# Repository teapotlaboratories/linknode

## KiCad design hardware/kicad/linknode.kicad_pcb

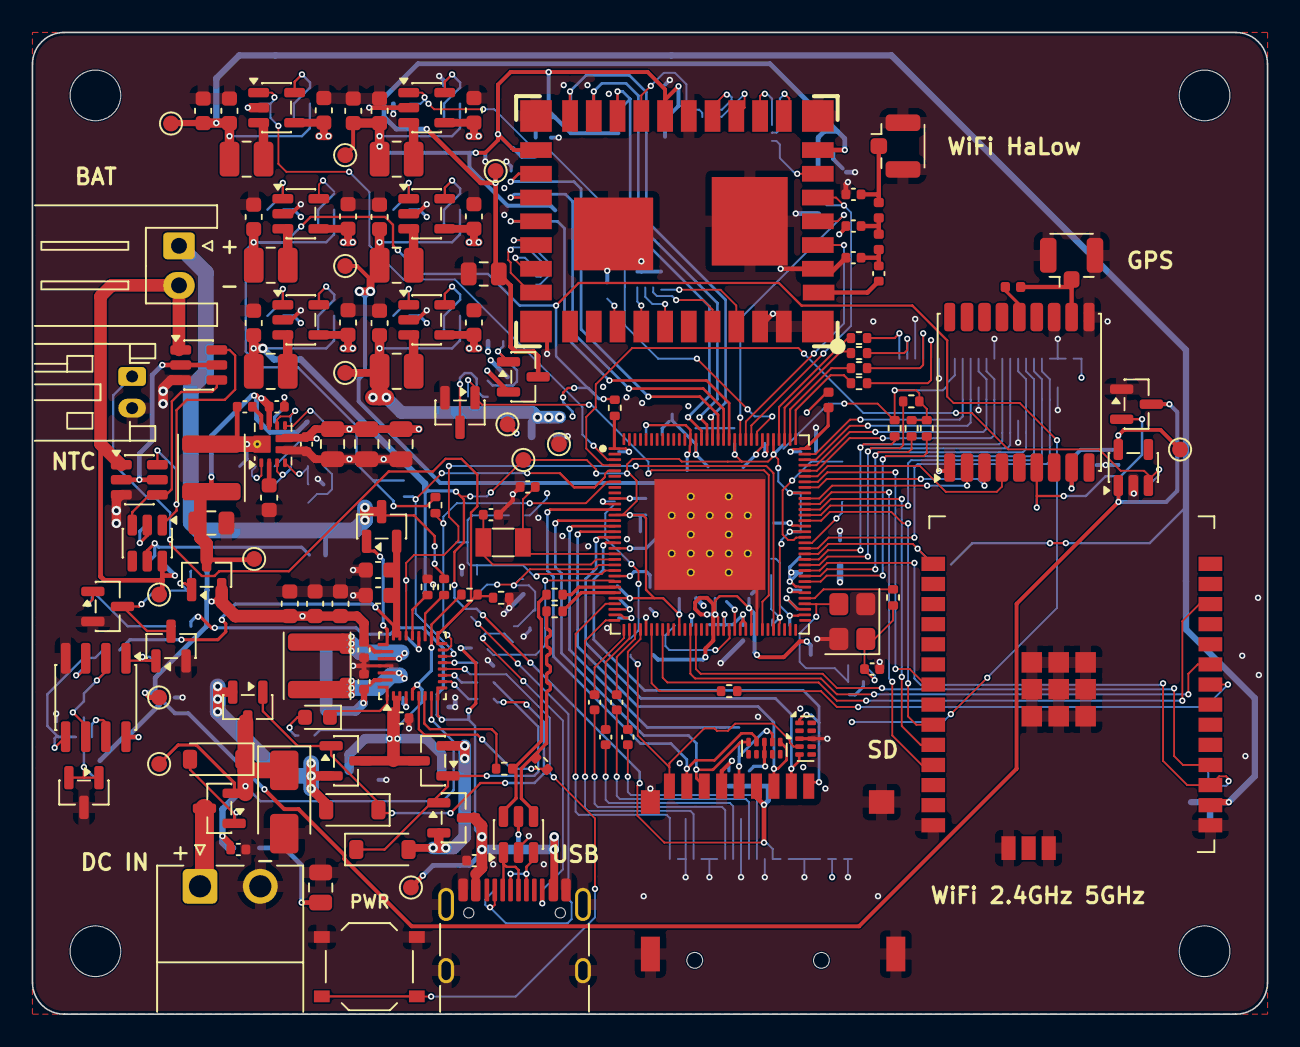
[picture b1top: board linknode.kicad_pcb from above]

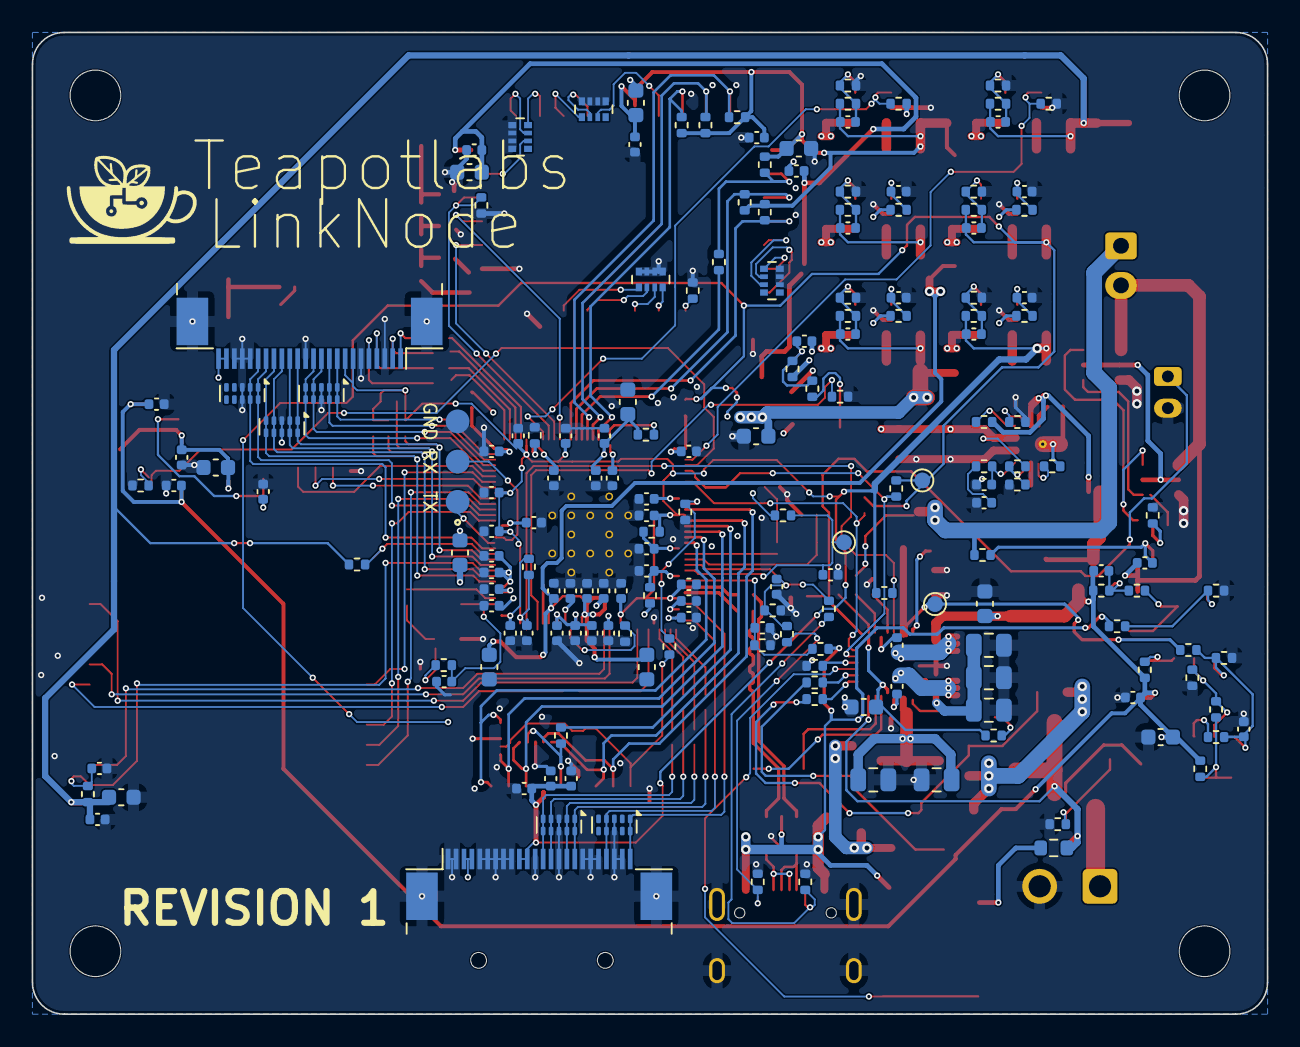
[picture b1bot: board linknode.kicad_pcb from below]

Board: 4 copper layers, 78.0 x 62.0 mm, 324 parts (181 on the bottom side), 199 nets.

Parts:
C1, C3, C6, C10: 100nF 50V; C_0402_1005Metric
C2: 2.2uF 50V; C_0805_2012Metric
C4, C5, C7, C8, C9, C24: 10uF 25V; C_0805_2012Metric
C11, C12: 47nF 50V; C_0402_1005Metric
C13, C50, C60, C70, C80, C100, C110: 4.7uF 16V; C_0603_1608Metric
C14, C15, C16, C17, C18, C20, C21, C53, C63, C73, C83, C102, C103, C112, C113, C202: 10uF 10V; C_0603_1608Metric
C19: 100nF 16V; C_0402_1005Metric
C23, C25, C26, C33, C61, C71, C81, C122, C301, C304, C402, C404, C506, C508, C601, C602, C603, C607, C612, C613, C614, C615, C616, C617, C618, C619, C620, C624, C625, C626, C629, C630, C631, C632, C633, C634, C635, C636, C701, C703, C705, C803: 100nF; C_0402_1005Metric
C27: 2.2uF; C_0603_1608Metric
C28: 6.8nF; C_0402_1005Metric
C29: 22pF; C_0402_1005Metric
C30, C31, C32, C121: 22uF 25V; C_0805_2012Metric
C51, C120, C302, C505: 10nF; C_0402_1005Metric
C52, C62, C72, C82, C101, C111: 6.8pF; C_0402_1005Metric
C200, C201, C203, C204: 1uF 25V; C_0402_1005Metric
C401, C637: 4.7uF; C_0402_1005Metric
C501, C502, C503, C504: 18pF C0G; C_0402_1005Metric
C507: 1nF; C_0402_1005Metric
C604, C606, C610, C611, C623, C627, C628, C801, C1001, C1002, C1003, C1004: 1uF; C_0402_1005Metric
C605, C608, C609, C621, C622, C702, C704, C706: 10uF; C_0603_1608Metric
C802: 22uF; C_0603_1608Metric
C901: 100pF C0G; C_0402_1005Metric
C902, C904: 2.7pF C0G; C_0402_1005Metric
C903: 5.6pF C0G; C_0402_1005Metric
D1: SMAJ24A; D_SMA
D2: CHG; LED_0603_1608Metric
D3: BZT52C12; D_SOD-123
D4, D5: BZT52C10; D_SOD-123
FB601: 120R@100MHz; L_0402_1005Metric
J1: TYPE-C-31-M-12; USB_C_Receptacle_HRO_TYPE-C-31-M-12
J2: DC IN 3.6-24V; Kefa_KF2EDGR-3.81-2P_Horizontal
J3: Battery 1S; JST_XH_S2B-XH-A_1x02_P2.50mm_Horizontal
J4: Pack NTC; JST_PH_S2B-PH-K_1x02_P2.00mm_Horizontal
J20: U.FL GPS; U.FL_Hirose_U.FL-R-SMT-1_Vertical
J401: TF PUSH; microSD_ShouHan_TF-PUSH
J501: DEBUG UART; TestPads_1x03_P2.54mm
J901: U.FL HaLow; U.FL_Hirose_U.FL-R-SMT-1_Vertical
J1001: FPC A 24P; Jushuo_AFC07-S24ECC-00_1x24-1MP_P0.50_Horizontal
J1002: FPC B 24P; Jushuo_AFC07-S24ECC-00_1x24-1MP_P0.50_Horizontal
L1: 2.2uH 3.2A; L_Changjiang_FNR4030S
L2: 2.2uH 7.5A; L_Changjiang_FNR4020S
L5, L6, L7, L8, L10, L11: 2.2uH 3A; L_1008_2520Metric
L20: 47nH; L_0402_1005Metric
L901, L902: 8.2nH; L_0402_1005Metric
LOGO1: LOGO; TeapotLogo
MH1, MH2, MH3, MH4: MountingHole_3.2mm_M3
Q1, Q2, Q13: AO3400A; SOT-23
Q3, Q4: SI2318A; SOT-23
Q5, Q6: FS8205A; SOT-23-6
Q7, Q9: AO3401A; SOT-23
Q8, Q10, Q12: 2N7002; SOT-23
Q11: WST2319; SOT-23
R1, R2: 5.1k; R_0402_1005Metric
R3: 2R; R_0603_1608Metric
R4, R11, R402, R603: 100R; R_0402_1005Metric
R5, R10, R121, R303, R307, R310, R504, R505, R506, R510, R701, R702, R703, R704, R705, R706, R707, R708, R801, R802: 10k; R_0402_1005Metric
R6, R1005, R1006, R1007, R1008: 4.7k; R_0402_1005Metric
R7: 5.23k; R_0402_1005Metric
R8: 30.1k; R_0402_1005Metric
R9: 2.2k; R_0402_1005Metric
R12, R503: 1k; R_0402_1005Metric
R13, R15: 316k; R_0402_1005Metric
R14: 180k; R_0402_1005Metric
R16, R18, R22, R23, R24, R25, R50, R52, R60, R62, R70, R72, R82, R100, R102, R110, R112, R120, R122, R200, R302, R304, R305, R306, R308, R311: 100k; R_0402_1005Metric
R17: 8.06k; R_0402_1005Metric
R19, R26, R27, R1001, R1002, R1003, R1004: 0R; R_0402_1005Metric
R20, R21: 294R; R_0402_1005Metric
R51: 47k; R_0402_1005Metric
R61: 124k; R_0402_1005Metric
R71, R80: 200k; R_0402_1005Metric
R81, R101, R111: 453k; R_0402_1005Metric
R301: 432k; R_0402_1005Metric
R309: 887k; R_0402_1005Metric
R403: 10k DNP; R_0402_1005Metric
R501, R511, R512, R513: 22R; R_0402_1005Metric
R502: 1M; R_0402_1005Metric
R507: 15k; R_0402_1005Metric
R508, R509: 2.2R; R_0402_1005Metric
R601, R602: 1R; R_0402_1005Metric
R604: 240R 1%; R_0402_1005Metric
R605: 6.04k 1%; R_0402_1005Metric
RN701, RN702, RN703, RN704: 4x10k; R_Array_Convex_4x0402
SW1: PWR; SW_Push_1P1T_XKB_TS-1187A
TP1: VBUS; TestPoint_Pad_D1.0mm
TP2: VDCIN; TestPoint_Pad_D1.0mm
TP3: VSYS; TestPoint_Pad_D1.0mm
TP4: VBAT; TestPoint_Pad_D1.0mm
TP5: GND; TestPoint_Pad_D1.0mm
TP6: CELL_N; TestPoint_Pad_D1.0mm
TP7: 5V0; TestPoint_Pad_D1.0mm
TP15: VDD_0V9; TestPoint_Pad_D1.0mm
TP16: VCC_DDR; TestPoint_Pad_D1.0mm
TP17: VCC_1V8; TestPoint_Pad_D1.0mm
TP18: VCC_3V3; TestPoint_Pad_D1.0mm
TP20: VCC3V3_C5; TestPoint_Pad_D1.0mm
TP21: VCC3V3_HALOW; TestPoint_Pad_D1.0mm
TP22: VDD_FEM; TestPoint_Pad_D1.0mm
TP23: VCC3V3_GPS; TestPoint_Pad_D1.0mm
TP31: VSYS_SW; TestPoint_Pad_D1.0mm
TP501: RECOVERY; TestPoint_Pad_D1.0mm
U1: USBLC6-2SC6; SOT-23-6
U2: BQ25798RQMR; Texas_RQM0029A_VQFN-29_4x4mm_P0.4mm
U3: DW01A; SOT-23-6
U4: TPS61089RNRR; Texas_VQFN-RNR0011A-11
U5, U6, U7, U8, U10, U11: TLV62569DBVR; SOT-23-5
U20: ATGM336H-5NR32-G; ublox_MAX
U21: ME6211C33M5G-N; SOT-23-5
U22: XC6206P332MR; SOT-23
U30: LM2903DR2G; SOIC-8_3.9x4.9mm_P1.27mm
U31: TL432 0.5%; SOT-23
U100: RV1106G3; Rockchip_QFN-128-1EP_12.3x12.3mm_P0.35mm_EP7x7mm
U401, U402, U1001, U1002, U1003, U1006, U1007: TPD4E05U06DQAR; USON-10_2.5x1.0mm_P0.5mm
U701: HT-HC01_V2
U801: ESP32-C5-WROOM-1U-N16R8; ESP32-C5-WROOM-1U
Y501: 24MHz; Crystal_SMD_3225-4Pin_3.2x2.5mm
Y502: 32.768kHz; Crystal_SMD_3215-2Pin_3.2x1.5mm

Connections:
/Antenna/HALOW_ANT: C901.1, U701.38
/Battery/SDRV: Q13.1, U2.24
/Battery/TS: J4.1, R7.2, R8.1, U2.16
/ESP32-C5/C5_BOOT: R802.2, U100.77, U801.15
/ESP32-C5/C5_DATA_READY: U100.83, U801.23
/ESP32-C5/C5_EN: C801.1, R801.2, U100.74, U801.3
/ESP32-C5/C5_HANDSHAKE: U100.90, U801.21
/ESP32-C5/C5_SPI_CLK: R512.2, U801.8
/ESP32-C5/C5_SPI_CS: U100.40, U801.12
/ESP32-C5/C5_SPI_MISO: U100.46, U801.4
/ESP32-C5/C5_SPI_MOSI: U100.45, U801.9
/ESP32-C5/C5_UART_RX: U100.85, U801.24
/ESP32-C5/C5_UART_TX: U100.86, U801.25
/Expansion/ETH_RXN: R1004.1, U100.97
/Expansion/ETH_RXP: R1003.1, U100.98
/Expansion/ETH_TXN: R1002.1, U100.99
/Expansion/ETH_TXP: R1001.1, U100.100
/Expansion/EXP_GPIO1_B1: J1001.19, U100.78, U1001.2, U1001.9
/Expansion/EXP_GPIO1_C7: J1001.18, U100.84, U1001.1, U1001.10
/Expansion/I2C0_SCL: J1001.15, R1008.1, U100.75, U1003.2, U1003.9
/Expansion/I2C0_SDA: J1001.14, R1007.2, U100.76, U1003.1, U1003.10
/Expansion/I2C2_SCL: J1001.17, R1006.1, U100.72, U1003.5, U1003.6
/Expansion/I2C2_SDA: J1001.16, R1005.2, U100.73, U1003.4, U1003.7
/Expansion/LINEOUT: J1002.24, U100.29, U1007.1, U1007.10
/Expansion/MIC0N: C1001.1, U100.33
/Expansion/MIC0P: C1002.1, U100.34
/Expansion/MIC1N: C1003.2, U100.35
/Expansion/MIC1P: C1004.2, U100.36
/Expansion/MICBIAS: J1002.21, U100.32, U1007.4, U1007.7
/Expansion/SPI0_CLK: J1001.10, U100.94, U1002.2, U1002.9
/Expansion/SPI0_CS0: J1001.9, U100.95, U1002.1, U1002.10
/Expansion/SPI0_MISO: J1001.12, U100.92, U1002.5, U1002.6
/Expansion/SPI0_MOSI: J1001.11, U100.93, U1002.4, U1002.7
/GPS/GPS_PPS: U20.4, U100.91
/GPS/GPS_PWR_EN: R200.1, U21.3, U100.4
/GPS/GPS_RXD: U20.3, U100.89
/GPS/GPS_TXD: U20.2, U100.87
/HaLow/HALOW_BUSY: R707.1, U100.105, U701.34
/HaLow/HALOW_RESET_N: U100.107, U701.35
/HaLow/HALOW_SDIO_CLK: R513.1, R701.2, U701.18
/HaLow/HALOW_SDIO_CMD: R702.2, U100.112, U701.21
/HaLow/HALOW_SDIO_D0: R703.2, U100.110, U701.17
/HaLow/HALOW_SDIO_D1: R704.2, U100.109, U701.16
/HaLow/HALOW_SDIO_D2: R705.2, U100.114, U701.23
/HaLow/HALOW_SDIO_D3: R706.2, U100.113, U701.22
/HaLow/HALOW_WAKE: U100.106, U701.36
/Radio Power/C5_PWR_EN: R100.1, U10.1, U100.3
/Radio Power/HALOW_FEM_EN: Q8.1, R122.1, U100.58
/Radio Power/HALOW_PWR_EN: R110.1, U11.1, U100.104
/SoC/CHG_INT: R10.1, U2.21, U100.60
/SoC/I2C_SCL: R504.2, U2.14, U100.5
/SoC/I2C_SDA: R505.1, U2.15, U100.7
/SoC/SD_CLK: J401.5, R511.1, U401.2
/SoC/SD_CMD: J401.3, U100.16, U401.1
/SoC/SD_D0: J401.7, U100.14, U401.5
/SoC/SD_D1: J401.8, U100.12, U401.4
/SoC/SD_D2: J401.1, U100.18, U402.1
/SoC/SD_D3: J401.2, U100.17, U402.5
/SoC/SD_DET: R402.1, R403.1, U100.11
/SoC/USB_CC_SENSE: C508.1, R23.1, R24.1, R25.1, U100.22
/SoC/USB_DN: R26.1, R509.2, U1.6
/SoC/USB_DP: R27.1, R508.2, U1.4
/SoC/USB_SOC_DN: R509.1, U100.26
/SoC/USB_SOC_DP: R508.1, U100.27
/USB and Charger/CHG_DN: R26.2, U2.7
/USB and Charger/CHG_DP: R27.2, U2.6
/USB and Charger/USB_CONN_DN: J1.A7, J1.B7, U1.1
/USB and Charger/USB_CONN_DP: J1.A6, J1.B6, U1.3
GND: C1.2, C2.2, C3.2, C4.2, C5.2, C6.2, C7.2, C8.2, C9.2, C10.2, C13.2, C14.2, C15.2, C16.2, C17.2, C18.2, C19.2, C20.2, C21.2, C24.2, C25.2, C27.2, C28.2, C29.2, C30.2, C31.2, C32.2, C33.2, C50.2, C51.2, C53.2, C60.2, C61.2, C63.2, C70.2, C71.2, C73.2, C80.2, C81.2, C83.2, C100.2, C102.2, C103.2, C110.2, C112.2, C113.2, C121.2, C122.2, C200.2, C201.2, C202.2, C203.2, C204.2, C301.2, C304.2, C401.2, C402.2, C404.2, C501.2, C502.2, C503.2, C504.2, C505.2, C506.2, C507.2, C508.2, C601.2, C602.2, C603.2, C604.2, C605.2, C606.2, C607.2, C608.2, C609.2, C610.2, C611.2, C612.2, C613.2, C614.2, C615.2, C616.2, C617.2, C618.2, C619.2, C620.2, C621.2, C622.2, C623.2, C624.2, C625.2, C626.2, C627.2, C628.2, C629.2, C630.2, C631.2, C632.2, C633.2, C634.2, C635.2, C636.2, C637.2, C701.2, C702.2, C703.2, C704.2, C705.2, C706.2, C801.2, C802.2, C803.2, C902.2, C903.2, C904.2, D1.2, J1.A1, J1.A12, J1.B1, J1.B12, J1.SH, J2.2, J4.2, J20.2, J401.6, J401.SH, J501.3, J901.2, J1001.3, J1001.6, J1001.13, J1001.20, J1001.21, J1001.22, J1001.MP, J1002.1, J1002.2, J1002.5, J1002.6, J1002.7, J1002.8, J1002.9, J1002.12, J1002.15, J1002.18, J1002.19, J1002.20, J1002.22, J1002.23, J1002.MP, Q5.3, Q6.3, Q8.2, Q10.2, Q12.2, R1.2, R2.2, R5.2, R6.2, R8.2, R12.2, R14.2, R16.2, R22.2, R25.2, R52.2, R62.2, R72.2, R82.2, R100.2, R102.2, R110.2, R112.2, R122.2, R200.2, R302.2, R305.2, R311.2, R403.2, R507.2, R604.2, R605.2, R707.2, R708.2, RN701.5, RN701.6, RN701.7, RN701.8, RN702.5, RN702.6, RN702.7, RN702.8, RN703.5, RN703.6, RN703.7, RN703.8, RN704.6, RN704.7, RN704.8, SW1.1, TP5.1, U1.2, U2.27, U4.5, U5.2, U6.2, U7.2, U8.2, U10.2, U11.2, U20.1, U20.10, U20.12, U21.2, U22.1, U30.4, U31.3, U100.37, U100.57, U100.129, U401.3, U401.8, U402.3, U402.8, U701.0, U701.1, U701.2, U701.3, U701.12, U701.20, U701.26, U701.31, U701.37, U801.1, U801.28, U801.29, U801.30, U801.32, U1001.3, U1001.8, U1002.3, U1002.8, U1003.3, U1003.8, U1006.3, U1006.8, U1007.3, U1007.8, Y501.2, Y501.4
unnamed: C2.1, R3.2
unnamed: C28.1, R17.2
unnamed: C501.1, R501.1, R502.1, Y501.1
unnamed: C901.2, C902.1, L901.1
unnamed: C903.1, L901.2, L902.1
unnamed: D2.2, R9.1
unnamed: D2.1, U2.1
unnamed: D3.2, Q11.1, R22.1
unnamed: D4.2, Q1.2, Q2.2
unnamed: D4.1, Q1.1, Q2.1, R20.1
unnamed: D5.2, Q3.2, Q4.2
unnamed: D5.1, Q3.1, Q4.1, R21.1
unnamed: J1.A5, R1.1, R23.2
unnamed: J1.B5, R2.1, R24.2
unnamed: J2.1, Q11.3
unnamed: C23.2, J3.2, Q5.1, Q6.1, TP6.1, U3.6
unnamed: J20.1, L20.2, U20.11
unnamed: J401.9, R402.2, U402.4
unnamed: J501.1, U100.79
unnamed: J501.2, U100.80
unnamed: C904.1, J901.1, L902.2
unnamed: J1001.1, R1001.2
unnamed: J1001.2, R1002.2
unnamed: J1001.4, R1003.2
unnamed: J1001.5, R1004.2
unnamed: C4.1, C5.1, C6.1, Q2.3, Q4.3, U2.2, U2.3
unnamed: Q5.2, Q5.5, Q6.2, Q6.5
unnamed: Q5.6, Q6.6, U3.1
unnamed: Q5.4, Q6.4, U3.3
unnamed: C120.1, Q7.1, R120.1, R121.1
unnamed: Q8.3, R121.2
unnamed: C302.2, Q9.1, R307.1, R308.2
unnamed: Q10.3, Q12.3, R307.2
unnamed: Q10.1, R306.2, U30.1
unnamed: Q12.1, R310.2, R311.1
unnamed: R309.2, U30.7
unnamed: RN701.1, U701.4
unnamed: RN701.2, U701.5
unnamed: RN701.3, U701.7
unnamed: RN701.4, U701.8
unnamed: RN702.2, U701.33
unnamed: RN702.3, U701.30
unnamed: RN702.4, U701.29
unnamed: RN703.1, U701.28
unnamed: RN703.2, U701.27
unnamed: RN703.3, U701.24
unnamed: RN704.1, U701.14
unnamed: RN704.2, U701.13
unnamed: RN704.3, U701.15
unnamed: R20.2, U2.11
unnamed: R21.2, U2.10
unnamed: R4.1, U2.18
unnamed: C11.1, U2.4
unnamed: C12.2, U2.19
unnamed: C13.1, R7.1, R9.2, U2.5, U2.17
unnamed: C7.1, C8.1, C9.1, C10.1, U2.29
unnamed: R6.1, U2.20
unnamed: C11.2, L1.1, U2.28
unnamed: C12.1, L1.2, U2.26
unnamed: R5.1, U2.13
unnamed: SW1.2, U2.12
unnamed: R12.1, U3.2
unnamed: C23.1, R11.2, U3.5
unnamed: C26.2, U4.10
unnamed: C29.1, R17.1, U4.4
unnamed: R18.2, U4.7
unnamed: R15.2, R16.1, U4.3
unnamed: R13.2, U4.1
unnamed: R14.1, U4.8
unnamed: C26.1, L2.2, R13.1, U4.11
unnamed: C27.1, U4.2
unnamed: C51.1, R50.2, U5.1
unnamed: C52.2, R51.2, R52.1, U5.5
unnamed: L5.1, U5.3
unnamed: C61.1, R60.2, U6.1
unnamed: C62.2, R61.2, R62.1, U6.5
unnamed: L6.1, U6.3
unnamed: C71.1, R70.2, U7.1
unnamed: C72.2, R71.2, R72.1, U7.5
unnamed: L7.1, U7.3
unnamed: C81.1, R80.2, U8.1
unnamed: C82.2, R81.2, R82.1, U8.5
unnamed: L8.1, U8.3
unnamed: C101.2, R101.2, R102.1, U10.5
unnamed: L10.1, U10.3
unnamed: C111.2, R111.2, R112.1, U11.5
unnamed: L11.1, U11.3
unnamed: C204.1, U20.6, U22.2
unnamed: L20.1, U20.14
unnamed: C301.1, R301.2, R302.1, R309.1, U30.3, U30.5
unnamed: R304.2, R305.1, U30.2, U30.6
unnamed: R303.2, R304.1, U31.1, U31.2
unnamed: R604.1, U100.52
unnamed: C603.1, R602.1, U100.1
unnamed: C601.1, FB601.1, U100.96
unnamed: C604.1, R603.1, U100.19
unnamed: C602.1, R601.1, U100.24
unnamed: R511.2, U100.15
unnamed: R512.1, U100.38
unnamed: R513.2, U100.111
unnamed: C503.1, U100.21, Y502.1
unnamed: C504.1, U100.20, Y502.2
unnamed: C502.1, R502.2, U100.68, Y501.3
unnamed: R501.2, U100.69
unnamed: C507.1, R510.1, TP501.1, U100.23
unnamed: C506.1, R506.1, R507.1, U100.25
unnamed: C505.1, R503.2, U100.66
unnamed: C637.1, U100.30
unnamed: R605.1, U100.102
unnamed: R708.1, U701.9
unnamed: C1001.2, J1002.17, U1006.1, U1006.10
unnamed: C1002.2, J1002.16, U1006.2, U1006.9
unnamed: C1003.1, J1002.14, U1006.4, U1006.7
unnamed: C1004.1, J1002.13, U1006.5, U1006.6
VBAT: C20.1, C21.1, Q13.2, R301.1, TP4.1, U2.22, U2.23
VBUS: C1.1, J1.A4, J1.A9, J1.B4, J1.B9, Q1.3, R310.1, R506.2, TP1.1, U1.5, U2.9
VCC3V3_C5: C101.1, C102.1, C103.1, C802.1, C803.1, L10.2, R101.1, R801.1, R802.1, TP20.1, U801.2
VCC3V3_GPS: C201.1, C202.1, TP23.1, U20.8, U21.5
VCC3V3_HALOW: C111.1, C112.1, C113.1, C701.1, C702.1, C703.1, C704.1, L11.2, R111.1, R701.1, R702.1, R703.1, R704.1, R705.1, R706.1, TP21.1, U701.19, U701.25
VCC5V0_SYS: C30.1, C31.1, C32.1, C33.1, C50.1, C60.1, C70.1, C80.1, C100.1, C110.1, C120.2, J1001.23, J1001.24, J1002.3, J1002.4, Q7.2, R15.1, R50.1, R60.1, R70.1, R80.1, R120.2, TP7.1, U4.6, U5.4, U6.4, U7.4, U8.4, U10.4, U11.4
VCC_1V8: C72.1, C73.1, C625.1, C626.1, C627.1, C628.1, FB601.2, L7.2, R71.1, R504.1, R505.2, R510.2, R601.2, R602.2, TP17.1, U100.31, U100.53, U100.70
VCC_3V3: C82.1, C83.1, C401.1, C402.1, C404.1, C629.1, C630.1, C631.1, C632.1, C633.1, C634.1, C635.1, C636.1, J401.4, J1001.7, J1001.8, J1002.10, J1002.11, L8.2, R10.2, R81.1, R503.1, R603.2, R1005.1, R1006.2, R1007.1, R1008.2, TP18.1, U100.13, U100.28, U100.43, U100.61, U100.81, U100.88, U100.101, U100.108
VCC_DDR: C62.1, C63.1, C621.1, C622.1, C623.1, C624.1, L6.2, R61.1, TP16.1, U100.49, U100.50, U100.56
VCELL: J3.1, Q13.3, R4.2, R11.1
VDCIN: C3.1, D1.1, D3.1, Q3.3, Q11.2, R3.1, TP2.1, U2.8
VDD_0V9: C52.1, C53.1, C608.1, C609.1, C610.1, C611.1, C612.1, C613.1, C614.1, C615.1, C616.1, C617.1, C618.1, C619.1, C620.1, L5.2, R19.1, R51.1, TP15.1, U100.10, U100.51, U100.54, U100.55, U100.67, U100.71, U100.82, U100.103, U100.116
VDD_ARM: C605.1, C606.1, C607.1, R19.2, U100.115
VDD_FEM: C121.1, C122.1, C705.1, C706.1, Q7.3, TP22.1, U701.32
VSYS: C14.1, C15.1, C16.1, C17.1, C18.1, C19.1, C200.1, C203.1, C302.1, C304.1, Q9.2, R303.1, R306.1, R308.1, TP3.1, U2.25, U21.1, U22.3, U30.8
VSYS_SW: C24.1, C25.1, L2.1, Q9.3, R18.1, TP31.1, U4.9

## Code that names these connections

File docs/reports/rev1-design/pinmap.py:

# (group, rv_pin_number, rv_gpio, rv_function, net, peer, peer_pin, note)
P=[
('SD card','15','GPIO3_A4','SDMMC_CLK','SD_CLK','microSD','CLK','22 Ω series (Rockchip guide Table 2-7)'),
('SD card','16','GPIO3_A5','SDMMC_CMD','SD_CMD','microSD','CMD',''),
('SD card','14','GPIO3_A3','SDMMC_D0','SD_D0','microSD','DAT0',''),
('SD card','12','GPIO3_A2','SDMMC_D1','SD_D1','microSD','DAT1',''),
('SD card','18','GPIO3_A7','SDMMC_D2','SD_D2','microSD','DAT2',''),
('SD card','17','GPIO3_A6','SDMMC_D3','SD_D3','microSD','CD/DAT3',''),
('SD card','11','GPIO3_A1','SDMMC_DET','SD_DET','microSD','card-detect switch','Low = card inserted, selects SDMMC over JTAG/UART (guide §2.1.4)'),
('HaLow','111','GPIO2_A2','SDIO_CLK_M0','HALOW_SDIO_CLK','HT-HC01 V2','PAD_18 MM_SDIO_CLK','22 Ω series (guide Table 2-8)'),
('HaLow','112','GPIO2_A3','SDIO_CMD_M0','HALOW_SDIO_CMD','HT-HC01 V2','PAD_21 MM_SDIO_CMD','10k–100k pull-up (Heltec pin notes)'),
('HaLow','110','GPIO2_A1','SDIO_D0_M0','HALOW_SDIO_D0','HT-HC01 V2','PAD_17 MM_SDIO_D0','pull-up'),
('HaLow','109','GPIO2_A0','SDIO_D1_M0','HALOW_SDIO_D1','HT-HC01 V2','PAD_16 MM_SDIO_D1','pull-up'),
('HaLow','114','GPIO2_A5','SDIO_D2_M0','HALOW_SDIO_D2','HT-HC01 V2','PAD_23 MM_SDIO_D2','pull-up'),
('HaLow','113','GPIO2_A4','SDIO_D3_M0','HALOW_SDIO_D3','HT-HC01 V2','PAD_22 MM_SDIO_D3','pull-up'),
('HaLow','107','GPIO2_A6','GPIO out','HALOW_RESET_N','HT-HC01 V2','PAD_35 RESET_N','active low'),
('HaLow','106','GPIO2_A7','GPIO out','HALOW_WAKE','HT-HC01 V2','PAD_36 WAKE',''),
('HaLow','105','GPIO2_B0','GPIO in','HALOW_BUSY','HT-HC01 V2','PAD_34 MM_GPIO_0 (BUSY)','needed for power save'),
('HaLow','104','GPIO2_B1','GPIO out','HALOW_PWR_EN','Radio Power','TLV62569 EN (VBAT + VDD_IO)','default pull-down keeps HaLow off at boot'),
('HaLow','72','GPIO1_A0','GPIO out','HALOW_FEM_EN','Radio Power','VDD_FEM P-FET switch','5 V front-end'),
('ESP32','94','GPIO1_C1','SPI0_CLK_M0','ESP32_SPI_CLK','ESP32-WROOM-32UE','GPIO18 (VSPICLK)','IO_MUX pins, ESP32 datasheet p.15'),
('ESP32','93','GPIO1_C2','SPI0_MOSI_M0','ESP32_SPI_MOSI','ESP32-WROOM-32UE','GPIO23 (VSPID)',''),
('ESP32','92','GPIO1_C3','SPI0_MISO_M0','ESP32_SPI_MISO','ESP32-WROOM-32UE','GPIO19 (VSPIQ)',''),
('ESP32','95','GPIO1_C0','SPI0_CS0_M0','ESP32_SPI_CS','ESP32-WROOM-32UE','GPIO5 (VSPICS0)','GPIO5 is a strap pin; CS idles high'),
('ESP32','91','GPIO1_C4','GPIO in','ESP32_HANDSHAKE','ESP32-WROOM-32UE','GPIO26','ESP ready for next transfer'),
('ESP32','90','GPIO1_C5','GPIO in','ESP32_DATA_READY','ESP32-WROOM-32UE','GPIO27','ESP has a frame for Linux'),
('ESP32','89','GPIO1_D0','UART3_TX_M1','ESP32_UART_RX','ESP32-WROOM-32UE','U0RXD (GPIO3)','console + esptool'),
('ESP32','87','GPIO1_D1','UART3_RX_M1','ESP32_UART_TX','ESP32-WROOM-32UE','U0TXD (GPIO1)',''),
('ESP32','83','GPIO1_C6','GPIO out (open drain)','ESP32_EN','ESP32-WROOM-32UE','EN','10k pull-up + 1 µF on EN'),
('ESP32','84','GPIO1_C7','GPIO out (open drain)','ESP32_BOOT','ESP32-WROOM-32UE','GPIO0','10k pull-up; low at reset = download mode (Table 6)'),
('ESP32','73','GPIO1_A1','GPIO out','ESP32_PWR_EN','Radio Power','TLV62569 EN',''),
('ESP32-C5','38','GPIO4_A7','SPI1_CLK_M0','C5_SPI_CLK','ESP32-C5-WROOM-1U','SPI slave CLK (GPIO matrix)','C5 pins chosen on its sheet'),
('ESP32-C5','45','GPIO4_A1','SPI1_MOSI_M0','C5_SPI_MOSI','ESP32-C5-WROOM-1U','SPI slave MOSI',''),
('ESP32-C5','46','GPIO4_A0','SPI1_MISO_M0','C5_SPI_MISO','ESP32-C5-WROOM-1U','SPI slave MISO',''),
('ESP32-C5','40','GPIO4_A5','SPI1_CS0_M0','C5_SPI_CS','ESP32-C5-WROOM-1U','SPI slave CS',''),
('ESP32-C5','44','GPIO4_A2','GPIO in','C5_HANDSHAKE','ESP32-C5-WROOM-1U','GPIO (TBD)',''),
('ESP32-C5','42','GPIO4_A3','GPIO in','C5_DATA_READY','ESP32-C5-WROOM-1U','GPIO (TBD)',''),
('ESP32-C5','85','GPIO1_D3','UART5_TX_M1','C5_UART_RX','ESP32-C5-WROOM-1U','U0RXD','console + esptool'),
('ESP32-C5','86','GPIO1_D2','UART5_RX_M1','C5_UART_TX','ESP32-C5-WROOM-1U','U0TXD',''),
('ESP32-C5','74','GPIO1_A2','GPIO out (open drain)','C5_EN','ESP32-C5-WROOM-1U','EN (CHIP_PU)','10k pull-up + 1 µF'),
('ESP32-C5','77','GPIO1_B0','GPIO out (open drain)','C5_BOOT','ESP32-C5-WROOM-1U','GPIO28','10k pull-up; low at reset = download mode (Table 4-3)'),
('ESP32-C5','75','GPIO1_A3','GPIO out','C5_PWR_EN','Radio Power','TLV62569 EN',''),
]

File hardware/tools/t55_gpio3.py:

"""T55 (owner, 2026-11-24: "Switch to 1.8 V west pins"): FPC B's GPIOs move from the 3.3 V south pins (GPIO4_A6/A4/A3/A2/B0 on
39/41/42/44/47, GPIO0_A3/A4 on 62/63), which are boxed in by the microSD bus and the ESP32-C5 SPI, to the free 1.8 V VCCIO7 pins on the
west edge. GPS_PWR_EN moves from pin 4 to pin 2 (same 1.8 V group and reset pull-down), so the six GPIOs sit on contiguous pins 4-9
and don't cross the two enables. Minimal text edits.
Usage: python3 t55_gpio3.py <kicad dir>
soc.kicad_sch:       pins 39/41/42/44/47/62/63: wire + hierarchical label removed, no-connect back on the pin end
soc_power.kicad_sch: pin 4 label GPS_PWR_EN -> EXP_GPIO3_C6; pin 2 new stub GPS_PWR_EN; pins 5-9 new stubs EXP_GPIO3_C7/D1/D0/D2/D3
linknode.kicad_sch:  the 7 old sheet pins on SoC and Expansion and their wires removed; Expansion's top edge 2.54 mm higher and its
                     10 top pins (+ SoC bottom pins, wires) 17.78 mm right; 6 new pins SoC Power right edge -> Expansion left edge."""
import sys, os, re, uuid
sys.path.insert(0, os.path.join(os.path.dirname(os.path.abspath(__file__)), 'schgen'))
import symlib
K = sys.argv[1]
U = lambda: str(uuid.uuid4())
def g(v): return ('%.2f' % v).rstrip('0').rstrip('.')
def close(s, i):
    d = 0
    for j, ch in enumerate(s[i:]):
        if ch == '(': d += 1
        elif ch == ')':
            d -= 1
            if d == 0: return i + j + 1
PINS = {p['num']: p for p in symlib.pins('linknode:RV1106G3')}
def end(s, pin):
    for m in re.finditer(r'\(symbol\s+\(lib_id "linknode:RV1106G3"\)\s+\(at ([\d.\-]+) ([\d.\-]+) (\d+)\)(.*?)\(unit (\d+)\)', s, re.S):
        if int(m.group(5)) == PINS[pin]['unit']:
            return symlib.endpoint((float(m.group(1)), float(m.group(2))), int(m.group(3)), PINS[pin])[:2]
    raise SystemExit('unit not on sheet: ' + pin)
def near(a, b): return abs(a - b) < 0.01
def block(s, i):   # the top-level (...) item that starts at the line containing index i
    st = s.rindex('\n\t(', 0, i + 3) + 1; return st, close(s, st)
def unstub(s, pin, name):
    x, y = end(s, pin)
    m = re.search(r'\n\t\(hierarchical_label "' + re.escape(name) + r'"', s); assert m, name
    st, en = block(s, m.start() + 1); lab = s[st:en]
    lx, ly = map(float, re.search(r'\(at ([\d.\-]+) ([\d.\-]+)', lab).groups())
    wires = [w for w in re.finditer(r'\n\t\(wire\s+\(pts\s+\(xy ([\d.\-]+) ([\d.\-]+)\) \(xy ([\d.\-]+) ([\d.\-]+)\)', s)
             if {(round(float(w.group(1)), 2), round(float(w.group(2)), 2)), (round(float(w.group(3)), 2), round(float(w.group(4)), 2))}
             == {(round(x, 2), round(y, 2)), (round(lx, 2), round(ly, 2))}]
    assert len(wires) == 1, (pin, name, len(wires))
    ws, we = block(s, wires[0].start() + 1)
    for a, b in sorted([(st, en), (ws, we)], reverse=True): s = s[:a - 1] + s[b:]
    nc = f'\n\t(no_connect\n\t\t(at {g(x)} {g(y)})\n\t\t(uuid "{U()}")\n\t)'
    k = s.index('\n\t(wire'); return s[:k] + nc + s[k:]
def stub(s, pin, name, shape, lx):
    x, y = end(s, pin)
    hits = [m for m in re.finditer(r'\n\t\(no_connect\n\t\t\(at ([\d.\-]+) ([\d.\-]+)\)\n\t\t\(uuid "[^"]+"\)\n\t\)', s)
            if near(float(m.group(1)), x) and near(float(m.group(2)), y)]
    assert len(hits) == 1, (pin, x, y, len(hits))
    s = s[:hits[0].start()] + s[hits[0].end():]
    rot = 180 if lx < x else 0; just = 'right' if rot == 180 else 'left'
    add = (f'\n\t(wire\n\t\t(pts\n\t\t\t(xy {g(x)} {g(y)}) (xy {g(lx)} {g(y)})\n\t\t)\n\t\t(stroke\n\t\t\t(width 0)\n\t\t\t(type default)\n\t\t)\n\t\t(uuid "{U()}")\n\t)'
           f'\n\t(hierarchical_label "{name}"\n\t\t(shape {shape})\n\t\t(at {g(lx)} {g(y)} {rot})\n\t\t(effects\n\t\t\t(font\n\t\t\t\t(size 1.27 1.27)\n\t\t\t)\n\t\t\t(justify {just})\n\t\t)\n\t\t(uuid "{U()}")\n\t)')
    k = s.index('\n\t(wire'); return s[:k] + add + s[k:]
OLD = [('39', 'EXP_GPIO4_A6'), ('41', 'EXP_GPIO4_A4'), ('42', 'EXP_GPIO4_A3'), ('44', 'EXP_GPIO4_A2'), ('47', 'EXP_GPIO4_B0'),
       ('62', 'EXP_GPIO0_A3'), ('63', 'EXP_GPIO0_A4')]
NEW = [('4', 'EXP_GPIO3_C6'), ('5', 'EXP_GPIO3_C7'), ('6', 'EXP_GPIO3_D1'), ('7', 'EXP_GPIO3_D0'), ('8', 'EXP_GPIO3_D2'), ('9', 'EXP_GPIO3_D3')]

p = os.path.join(K, 'soc.kicad_sch'); s = open(p).read()
for pin, name in OLD: s = unstub(s, pin, name)
open(p, 'w').write(s)

p = os.path.join(K, 'soc_power.kicad_sch'); s = open(p).read()
pat = re.compile(r'\(hierarchical_label "GPS_PWR_EN"\s+\(shape \w+\)'); assert len(pat.findall(s)) == 1
s = pat.sub('(hierarchical_label "EXP_GPIO3_C6"\n\t\t(shape bidirectional)', s)
s = stub(s, '2', 'GPS_PWR_EN', 'output', 182.88)
for pin, name in NEW[1:]: s = stub(s, pin, name, 'bidirectional', 182.88)
open(p, 'w').write(s)

p = os.path.join(K, 'linknode.kicad_sch'); s = open(p).read()
def sheet_span(s, name):
    i = s.index(f'(property "Sheetname" "{name}"'); st = s.rindex('\n\t(sheet\n', 0, i) + 1; return st, close(s, st)
def drop_pin(s, sheet, name):
    st, en = sheet_span(s, sheet); blk = s[st:en]
    m = re.search(r'\n\t\t\(pin "' + re.escape(name) + r'" \w+', blk); assert m, (sheet, name)
    b = close(blk, m.start() + 3)                       # m starts at '\n\t\t(pin'
    return s[:st] + blk[:m.start()] + blk[b:] + s[en:]
for _, name in OLD:
    st, en = sheet_span(s, 'SoC'); x = float(re.search(r'\(pin "' + name + r'" \w+\s+\(at ([\d.]+) ', s[st:en]).group(1))
    s = drop_pin(s, 'SoC', name); s = drop_pin(s, 'Expansion', name)
    w = [m for m in re.finditer(r'\n\t\(wire\s+\(pts\s+\(xy ([\d.]+) 139\.7\) \(xy ([\d.]+) 147\.32\)', s)
         if near(float(m.group(1)), x) and near(float(m.group(2)), x)]
    assert len(w) == 1, (name, x); ws, we = block(s, w[0].start() + 1); s = s[:ws - 1] + s[we:]
# Expansion's top edge moves up 2.54 (six free left-edge slots at 147.32..160.02); its 10 remaining top pins, the matching SoC
# bottom pins and their wires move 17.78 right into the freed slots, so their vertical text clears the new left-edge pin text
st, en = sheet_span(s, 'Expansion'); blk = s[st:en]
nb = re.sub(r'\(at 101\.6 147\.32\)(\s+\(size 63\.5 )40\.64\)', r'(at 101.6 144.78)\g<1>43.18)', blk, count=1); assert nb != blk
nb2 = re.sub(r'(\(property "Sheetname" "Expansion"\s+\(at 147\.32 )146\.05', r'\g<1>143.51', nb, count=1); assert nb2 != nb
s = s[:st] + nb2 + s[en:]
KEEP = ['I2C2_SDA', 'I2C2_SCL', 'I2C0_SDA', 'I2C0_SCL', 'SPI0_CS0', 'SPI0_CLK', 'SPI0_MOSI', 'SPI0_MISO', 'EXP_GPIO1_B1', 'EXP_GPIO1_C7']
for name in KEEP:
    for sheet in ('SoC', 'Expansion'):
        st, en = sheet_span(s, sheet); blk = s[st:en]
        m = re.search(r'(\(pin "' + re.escape(name) + r'" \w+\s+\(at )([\d.]+) ([\d.]+)', blk); assert m, (sheet, name)
        x, y = float(m.group(2)), float(m.group(3)); ny = 144.78 if sheet == 'Expansion' else y
        blk = blk[:m.start()] + m.group(1) + f'{g(x + 17.78)} {g(ny)}' + blk[m.end():]
        s = s[:st] + blk + s[en:]
    w = re.compile(r'\(xy ' + re.escape(g(x)) + r' 139\.7\) \(xy ' + re.escape(g(x)) + r' 147\.32\)'); assert len(w.findall(s)) == 1, name
    s = w.sub(f'(xy {g(x + 17.78)} 139.7) (xy {g(x + 17.78)} 144.78)', s)
def pin_txt(name, x, y, rot):
    just = 'right' if rot == 0 else 'left'
    return (f'\n\t\t(pin "{name}" bidirectional\n\t\t\t(at {g(x)} {g(y)} {rot})\n\t\t\t(uuid "{U()}")\n\t\t\t(effects\n\t\t\t\t(font\n\t\t\t\t\t(size 1.27 1.27)\n\t\t\t\t)\n\t\t\t\t(justify {just})\n\t\t\t)\n\t\t)')
YS = [147.32, 149.86, 152.4, 154.94, 157.48, 160.02]
for sheet, x, rot in (('SoC Power', 71.12, 0), ('Expansion', 101.6, 180)):
    st, en = sheet_span(s, sheet); blk = s[st:en]
    k = blk.index('\n\t\t(pin '); blk = blk[:k] + ''.join(pin_txt(n, x, y, rot) for (_, n), y in zip(NEW, YS)) + blk[k:]
    s = s[:st] + blk + s[en:]
add = ''.join(f'\n\t(wire\n\t\t(pts\n\t\t\t(xy 71.12 {g(y)}) (xy 101.6 {g(y)})\n\t\t)\n\t\t(stroke\n\t\t\t(width 0)\n\t\t\t(type default)\n\t\t)\n\t\t(uuid "{U()}")\n\t)' for y in YS)
k = s.index('\n\t(wire'); s = s[:k] + add + s[k:]
open(p, 'w').write(s)
print('soc: 7 stubs removed; soc_power: 1 rename + 6 stubs; root: 7 pins x2 + 7 wires removed, Expansion top up 2.54, 10 pins x2 + wires 17.78 right, 6 pins x2 + 6 wires added')
